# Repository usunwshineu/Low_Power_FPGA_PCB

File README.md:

# ICE40UP5K LOW POWER FPGA BOARD 

## PCB design

A custom low-power FPGA development board based on the Lattice iCE40UP5K FPGA. 
The board was designed to provide FPGA processing capabilities together with 
power monitoring and common communication interfaces.

The board contains:
* ICE40UP5K FPGA
* FTDI USB interface
* 12MHz clock (used for both the FPGA and FTDI)
* INA226 sensors for measuring power consumption
* I2C and SPI mode 0 PMODs
* SPI Flash memory
* I/O pins
* a reset button
* 3 buttons
* 4 LEDs and 1 RGB LED
  
For different SPI modes you can check <a href="https://0x04.net/~mwk/sbdocs/ice40/FPGA-TN-02010-1-8-iCE40-I2C-and-SPI-Hardened-IP-User-Guide.pdf">this document.

The final assembled board:

## PCB programming 

I checked the functionality of the board by running some simple verilog and I used icestorm for creating the bitstream. 
You can check more about Project IceStorm here <a href="https://0x04.net/~mwk/sbdocs/ice40/FPGA-TN-02010-1-8-iCE40-I2C-and-SPI-Hardened-IP-User-Guide.pdf](https://prjicestorm.readthedocs.io/en/latest/overview.html#what-is-project-icestorm">.

The commands I used were: 
* yosys -p "synth_ice40 -top top -json module.json" module.v -> for synthesizing the verilog design
* nextpnr-ice40 --up5k --package sg48 --json module.json --pcf pins.pcf --asc module.asc -> place-and-route
* icepack module.asc module.bin -> converting the result into binary bitstream
* iceprog module.bin -> programming the SPI Flash

Replace module.v, module.json, module.asc, module.bin, and pins.pcf with the corresponding filenames for your design.

## Adding a microprocessor

I used this particular RISC V system, which was built specifically for iCE40UP5k FPGAs: <a href="https://github.com/emeb/up5k_riscv/blame/master/README.md">up5k_riscv.

I modified the icestorm/up5k_riscv.pcf file with my own pins. Any other modified files were added to this repository.
In main.c file I wrote a code to read the power consumption (using I2C communication with the INA226 sensors) and display it on an OLED (SPI communication). 

This provides a complete demonstration of the board's:

* RISC V processing system
* I2C communication
* SPI communication
* Power monitoring
* OLED display interface

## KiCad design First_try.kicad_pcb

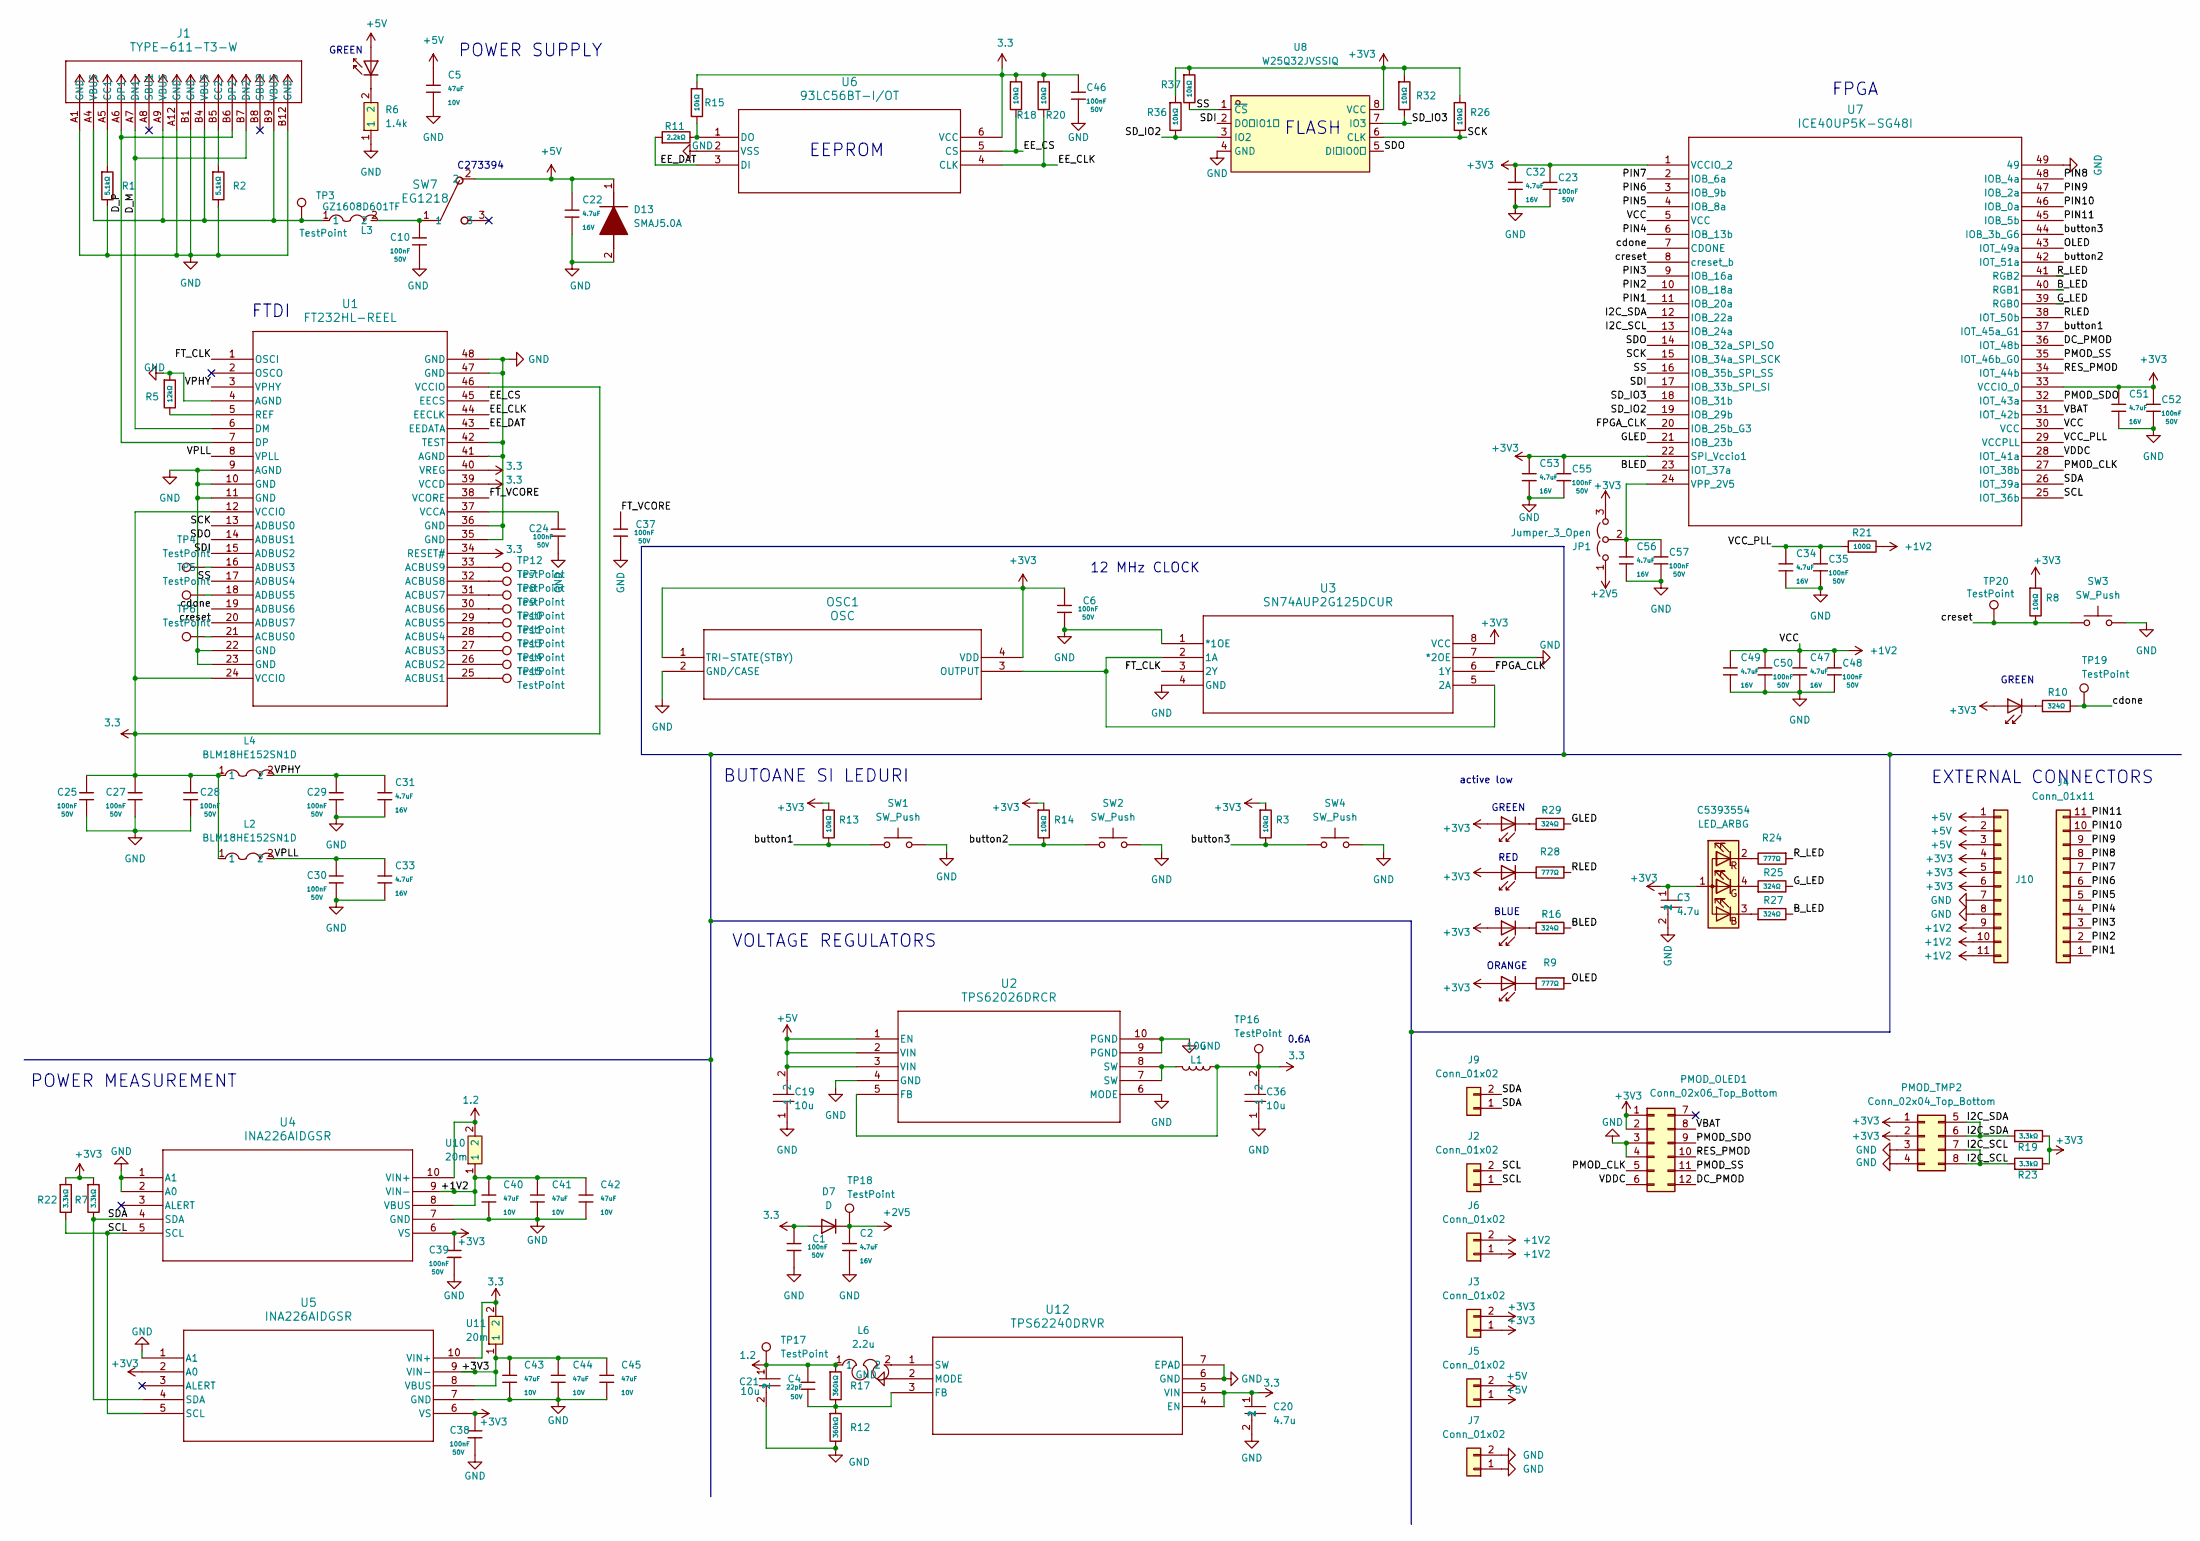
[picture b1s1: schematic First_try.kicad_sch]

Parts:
C1, C6, C10, C23, C24, C25, C27, C28, C29, C30, C35, C37, C38, C39, C46, C48, C50, C52, C55, C57: 100nF; C_0603; Voltage Rated 50V; Tolerance ±10%; Part CC0603KRX7R9BB104; LCSC C14663
C2, C22, C31, C32, C33, C34, C47, C49, C51, C53, C56: 4.7uF; C_0603; Voltage Rated 16V; Tolerance ±10%; Part CL10A475KO8NNNC; LCSC C19666
C3, C20: 4.7u; C_0603; LCSC Part C71631
C4: 22pF; C_0603; Voltage Rated 50V; Tolerance ±5%; Part CL10C220JB8NNNC; LCSC C1653
C5, C40, C41, C42, C43, C44, C45: 47uF; C_1206; Voltage Rated 10V; Tolerance ±20%; Part CL31A476MPHNNNE; LCSC C96123
C19, C36: 10u; C_1206; LCSC Part C92789
C21: 10u; C_0603; LCSC Part C77041
C5393554: LED_ARBG; RGB_LED; JLCPCB C5393554
D1, D2, D3: LD274; LED-SMD_L1.0-W0.5-RD; JLCPCB C5875752
D4: LD274; D_0805; JLCPCB C5366382
D5: LD274; LED-SMD_L1.0-W0.5-RD; JLCPCB C5354973
D6: LD274; LED-SMD_L2.1-W1.0-FD_UMD960; JLCPCB C5588281
D7: D; D2V5; JLCPCB C727112
D13: SMAJ5.0A; SMAJ; Manufacturer_Part_Number SMAJ5.0A; Mouser Part Number 652-SMAJ5.0A
J1: TYPE-611-T3-W; USB_C_Receptacle_HCTL_HC-TYPE-C-16P-01A; JLCPCB C2689844
J2, J3, J5, J6, J7, J9: Conn_01x02; PinHeader_1x02_P2.54mm_Vertical; JLCPB C32713268
J4, J10: Conn_01x11; PinHeader_1x11_P2.54mm_Vertical
JP1: Jumper_3_Open; PinHeader_1x03_P1.27mm_Vertical; JLCPCB C24980
L1: 10u; L_APV_ANR6045; JLCPCB C5259068
L2, L4: BLM18HE152SN1D; L_0603; LCSC Part C82155
L3: GZ1608D601TF; L_0603; LCSC Part C1002
L6: 2.2u; IND-SMD_L3.0-W3.0_LPS3015-222ML; LCSC Part C2844756
OSC1: OSC; ASE-3.2X2.5_ABR; JLCPCB C596950
PMOD_OLED1: Conn_02x06_Top_Bottom; PinSocket_2x06_P2.54mm_Horizontal_edit; JLCPCB C5333437
PMOD_TMP2: Conn_02x04_Top_Bottom; PinSocket_2x04_P2.54mm_Horizontal_edit; JLCPCB C7529541
R1, R2: 5.1kΩ; R_0603; Overload Voltage (Max) 75V; Tolerance ±1%; Part 0603WAF5101T5E; LCSC C23186
R3, R8, R13, R14, R15, R18, R20, R26, R32, R36, R37: 10kΩ; R_0603; Overload Voltage (Max) 75V; Tolerance ±1%; Part 0603WAF1002T5E; LCSC C25804
R5: 12kΩ; R_0603; Overload Voltage (Max) 75V; Tolerance ±1%; Part 0603WAF1202T5E; LCSC C22790
R6: 1.4k; R_0603; LCSC Part C25957
R7, R19, R22, R23: 3.3kΩ; R_0603; Overload Voltage (Max) 75V; Tolerance ±1%; Part 0603WAF3301T5E; LCSC C22978
R9, R24, R28: 777Ω; R_0402; Overload Voltage (Max) 75V; Tolerance ±1%; Part 0603WAF1001T5E; LCSC C852914
R10, R16, R25, R27, R29: 324Ω; R_0603; Overload Voltage (Max) 75V; Tolerance ±1%; Part 0603WAF5600T5E; LCSC C12963
R11: 2.2kΩ; R_0603; Overload Voltage (Max) 75V; Tolerance ±1%; Part 0603WAF2201T5E; LCSC C4190
R12, R17: 360kΩ; R_0603; Overload Voltage (Max) 75V; Tolerance ±1%; Part 0603WAF3603T5E; LCSC C23146
R21: 100Ω; R_0603; Overload Voltage (Max) 75V; Tolerance ±1%; Part 0603WAF1000T5E; LCSC C22775
SW1, SW2, SW3, SW4: SW_Push; SW_push; JLCPCB C455095
SW7: EG1218; SW_1218_EWI; JLCPCB C273394
TP3, TP4, TP5, TP6, TP7, TP8, TP9, TP10, TP11, TP12, TP13, TP14, TP15, TP16, TP17, TP18, TP19, TP20: TestPoint; TestPoint_Pad_1.0x1.0mm
U1: FT232HL-REEL; FTDI; JLCPCB C51997
U2: TPS62026DRCR; Vreg3_3; JLCPCB C2071183
U3: SN74AUP2G125DCUR; Buffer; JLCPCB C2862074
U4, U5: INA226AIDGSR; INA226; JLCPCB C49851
U6: 93LC56BT-I/OT; EEPROM; JLCPCB C190271
U7: ICE40UP5K-SG48I; QFN48_L-ASC10_ICE40ULTRAPLUS_MACHXO2_LAT
U8: W25Q32JVSSIQ; FLASH; LCSC Part C82344
U10, U11: 20m; R20m; LCSC Part C4944045
U12: TPS62240DRVR; Vreg1_2; JLCPCB C398345

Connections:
1.2: C4.1, C21.1, L6.1, R17.1, TP17.1, U4.10 (VIN+), U10.2
3.3: C1.1, C20.1, C25.1, C27.1, C28.1, C36.2, C46.1, D7.2 (A), L1.1, L2.1, L4.1, R15.1, R18.1, R20.1, TP16.1, U1.12 (VCCIO), U1.24 (VCCIO), U1.34 (RESET#), U1.39 (VCCD), U1.40 (VREG), U1.46 (VCCIO), U2.5 (FB), U5.10 (VIN+), U6.6 (VCC), U11.2, U12.4 (EN), U12.5 (VIN)
+1V2: C40.1, C41.1, C42.1, C47.1, C48.1, C49.1, C50.1, J6.1, J6.2, J10.9, J10.10, J10.11, R21.2, U4.8 (VBUS), U4.9 (VIN-), U7.5 (VCC), U7.30 (VCC), U10.1
+2V5: C2.1, D7.1 (K), JP1.1 (A), TP18.1
+3V3: C3.1, C6.1, C23.1, C32.1, C38.1, C39.1, C43.1, C44.1, C45.1, C51.1, C52.1, C53.1, C55.1, C5393554.1 (A), D1.2 (A), D3.2 (A), D4.2 (A), D5.2 (A), D6.2 (A), J3.1, J3.2, J10.4, J10.5, J10.6, JP1.3 (B), OSC1.1 (TRI-STATE(STBY)), OSC1.4 (VDD), PMOD_OLED1.1, PMOD_OLED1.2, PMOD_TMP2.1, PMOD_TMP2.2, R3.1, R7.1, R8.1, R13.1, R14.1, R19.2, R22.1, R23.2, R26.1, R32.1, R36.1, R37.1, U3.8 (VCC), U4.6 (VS), U5.2 (A0), U5.6 (VS), U5.8 (VBUS), U5.9 (VIN-), U7.1 (VCCIO_2), U7.22 (SPI_Vccio1), U7.33 (VCCIO_0), U8.8 (VCC), U11.1; also elsewhere on the board
+5V: C5.1, C19.2, C22.1, D2.2 (A), D13.1 (K), J5.1, J5.2, J10.1, J10.2, J10.3, SW7.2, U2.1 (EN), U2.2 (VIN), U2.3 (VIN)
/BLED: R16.2, U7.23 (IOT_37a)
/B_LED: R27.2, U7.40 (RGB1)
/DC_PMOD: PMOD_OLED1.12, U7.36 (IOT_48b)
/D_M: J1.A7 (DN1), J1.B7 (DN2), U1.6 (DM)
/D_P: J1.A6 (DP1), J1.B6 (DP2), U1.7 (DP)
/EE_CLK: R20.2, U1.44 (EECLK), U6.4 (CLK)
/EE_CS: R18.2, U1.45 (EECS), U6.5 (CS)
/EE_DAT: R11.1, U1.43 (EEDATA), U6.3 (DI)
/FPGA_CLK: U3.6 (1Y), U7.20 (IOB_25b_G3)
/FT_CLK: U1.1 (OSCI), U3.3 (2Y)
/FT_VCORE: C37.1, U1.38 (VCORE)
/GLED: R29.2, U7.21 (IOB_23b)
/G_LED: R25.2, U7.39 (RGB0)
/I2C_SCL: PMOD_TMP2.7, PMOD_TMP2.8, R23.1, U7.13 (IOB_24a)
/I2C_SDA: PMOD_TMP2.5, PMOD_TMP2.6, R19.1, U7.12 (IOB_22a)
/OLED: R9.1, U7.43 (IOT_49a)
/PIN1: J4.1, U7.11 (IOB_20a)
/PIN2: J4.2, U7.10 (IOB_18a)
/PIN3: J4.3, U7.9 (IOB_16a)
/PIN4: J4.4, U7.6 (IOB_13b)
/PIN5: J4.5, U7.4 (IOB_8a)
/PIN6: J4.6, U7.3 (IOB_9b)
/PIN7: J4.7, U7.2 (IOB_6a)
/PIN8: J4.8, U7.48 (IOB_4a)
/PIN9: J4.9, U7.47 (IOB_2a)
/PIN10: J4.10, U7.46 (IOB_0a)
/PIN11: J4.11, U7.45 (IOB_5b)
/PMOD_CLK: PMOD_OLED1.5, U7.27 (IOT_38b)
/PMOD_SDO: PMOD_OLED1.9, U7.32 (IOT_43a)
/PMOD_SS: PMOD_OLED1.11, U7.35 (IOT_46b_G0)
/RES_PMOD: PMOD_OLED1.10, U7.34 (IOT_44b)
/RLED: R28.1, U7.38 (IOT_50b)
/R_LED: R24.1, U7.41 (RGB2)
/SCK: R26.2, U1.13 (ADBUS0), U7.15 (IOB_34a_SPI_SCK), U8.6 (CLK)
/SCL: J2.1, J2.2, R22.2, U4.5 (SCL), U5.5 (SCL), U7.25 (IOT_36b)
/SDA: J9.1, J9.2, R7.2, U4.4 (SDA), U5.4 (SDA), U7.26 (IOT_39a)
/SDI: U1.15 (ADBUS2), U7.17 (IOB_33b_SPI_SI), U8.2 (DO（IO1）)
/SDO: U1.14 (ADBUS1), U7.14 (IOB_32a_SPI_SO), U8.5 (DI（IO0）)
/SD_IO2: R36.2, U7.19 (IOB_29b), U8.3 (IO2)
/SD_IO3: R32.2, U7.18 (IOB_31b), U8.7 (IO3)
/SS: R37.2, U1.17 (ADBUS4), U7.16 (IOB_35b_SPI_SS), U8.1 (~CS)
/VBAT: PMOD_OLED1.8, U7.31 (IOT_42b)
/VCC_PLL: C34.1, C35.1, R21.1, U7.29 (VCCPLL)
/VDDC: PMOD_OLED1.6, U7.28 (IOT_41a)
/VPHY: C29.1, C31.1, L4.2, U1.3 (VPHY)
/VPLL: C30.1, C33.1, L2.2, U1.8 (VPLL)
/cdone: R10.2, TP19.1, U1.19 (ADBUS6), U7.7 (CDONE)
unnamed: C10.1, L3.2, SW7.1
unnamed: C5393554.3 (BK), R27.1
unnamed: C5393554.4 (GK), R25.1
unnamed: C5393554.2 (RK), R24.2
unnamed: D1.1 (K), R29.1
unnamed: D2.1 (K), R6.2
unnamed: D3.1 (K), R10.1
unnamed: D4.1 (K), R28.2
unnamed: D5.1 (K), R16.1
unnamed: D6.1 (K), R9.2
unnamed: J1.A5 (CC1), R1.1
unnamed: J1.B5 (CC2), R2.1
unnamed: J1.A4 (VBUS), J1.A9 (VBUS), J1.B4 (VBUS), J1.B9 (VBUS), L3.1, TP3.1
unnamed: C56.1, C57.1, JP1.2 (C), U7.24 (VPP_2V5)
unnamed: L1.2, U2.7 (SW), U2.8 (SW)
unnamed 68: OSC1.3 (OUTPUT), U3.2 (1A), U3.5 (2A); also elsewhere on the board
unnamed: TP6.1, U1.21 (ACBUS0)
unnamed: TP15.1, U1.25 (ACBUS1)
unnamed: TP14.1, U1.26 (ACBUS2)
unnamed: TP13.1, U1.27 (ACBUS3)
unnamed: TP11.1, U1.28 (ACBUS4)
unnamed: TP10.1, U1.29 (ACBUS5)
unnamed: TP9.1, U1.30 (ACBUS6)
unnamed: TP8.1, U1.31 (ACBUS7)
unnamed: TP7.1, U1.32 (ACBUS8)
unnamed: TP12.1, U1.33 (ACBUS9)
unnamed: TP4.1, U1.16 (ADBUS3)
unnamed: TP5.1, U1.18 (ADBUS5)
unnamed: R5.2, U1.5 (REF)
unnamed: C24.1, U1.37 (VCCA)
unnamed: R11.2, R15.2, U6.1 (DO)
unnamed: C4.2, R12.1, R17.2, U12.3 (FB)
unnamed: L6.2, U12.1 (SW)

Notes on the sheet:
POWER SUPPLY
C273394
ORANGE
FPGA
BLUE
EXTERNAL CONNECTORS
RED
EEPROM
GREEN
FTDI
GREEN
BUTOANE SI LEDURI
POWER MEASUREMENT
12 MHz CLOCK
0.6A
VOLTAGE REGULATORS
active low
FLASH

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
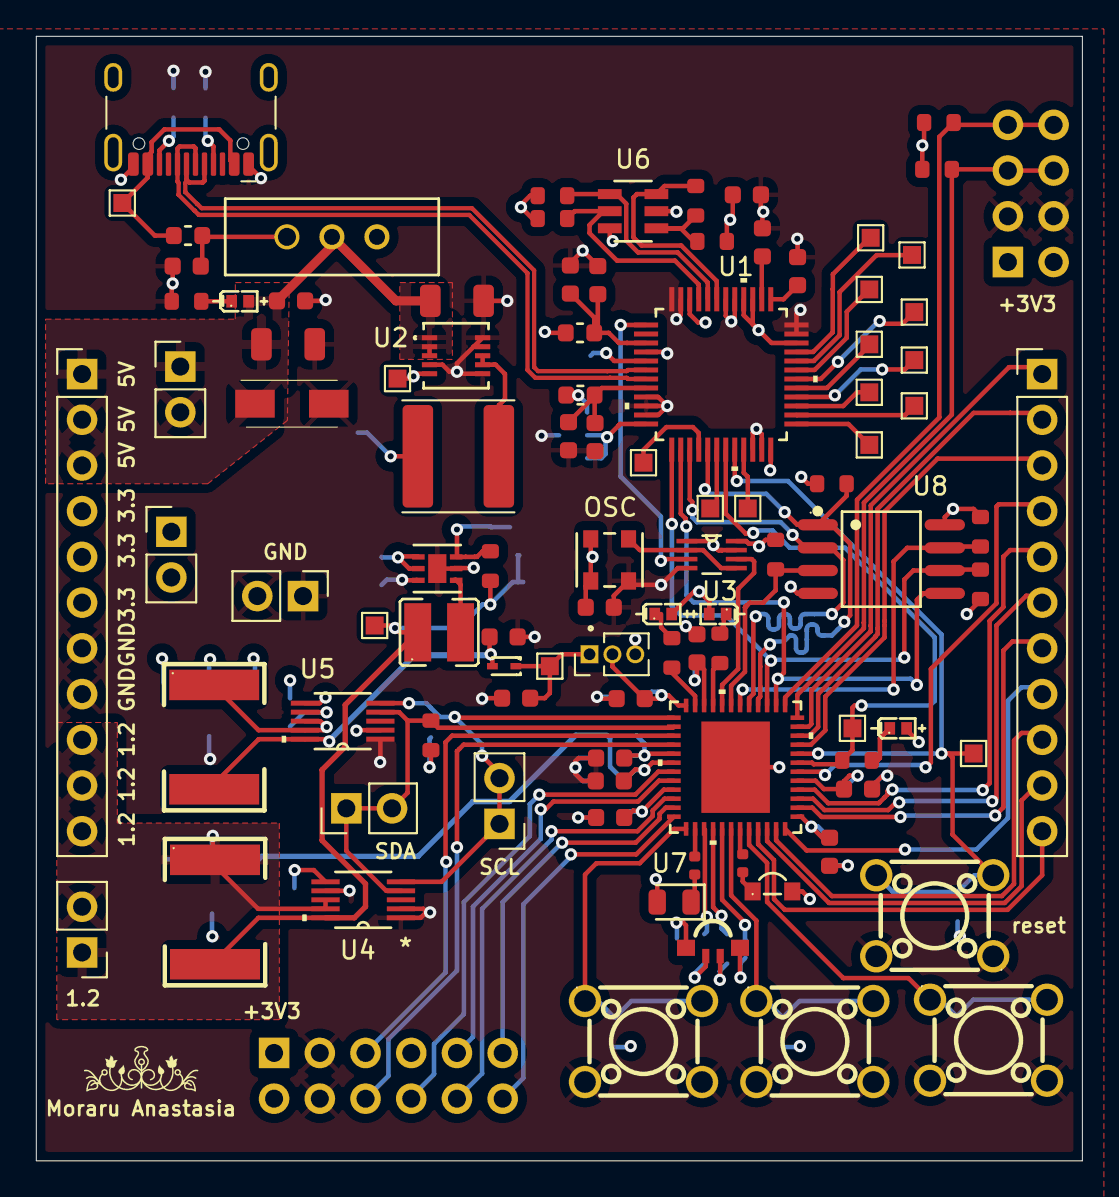
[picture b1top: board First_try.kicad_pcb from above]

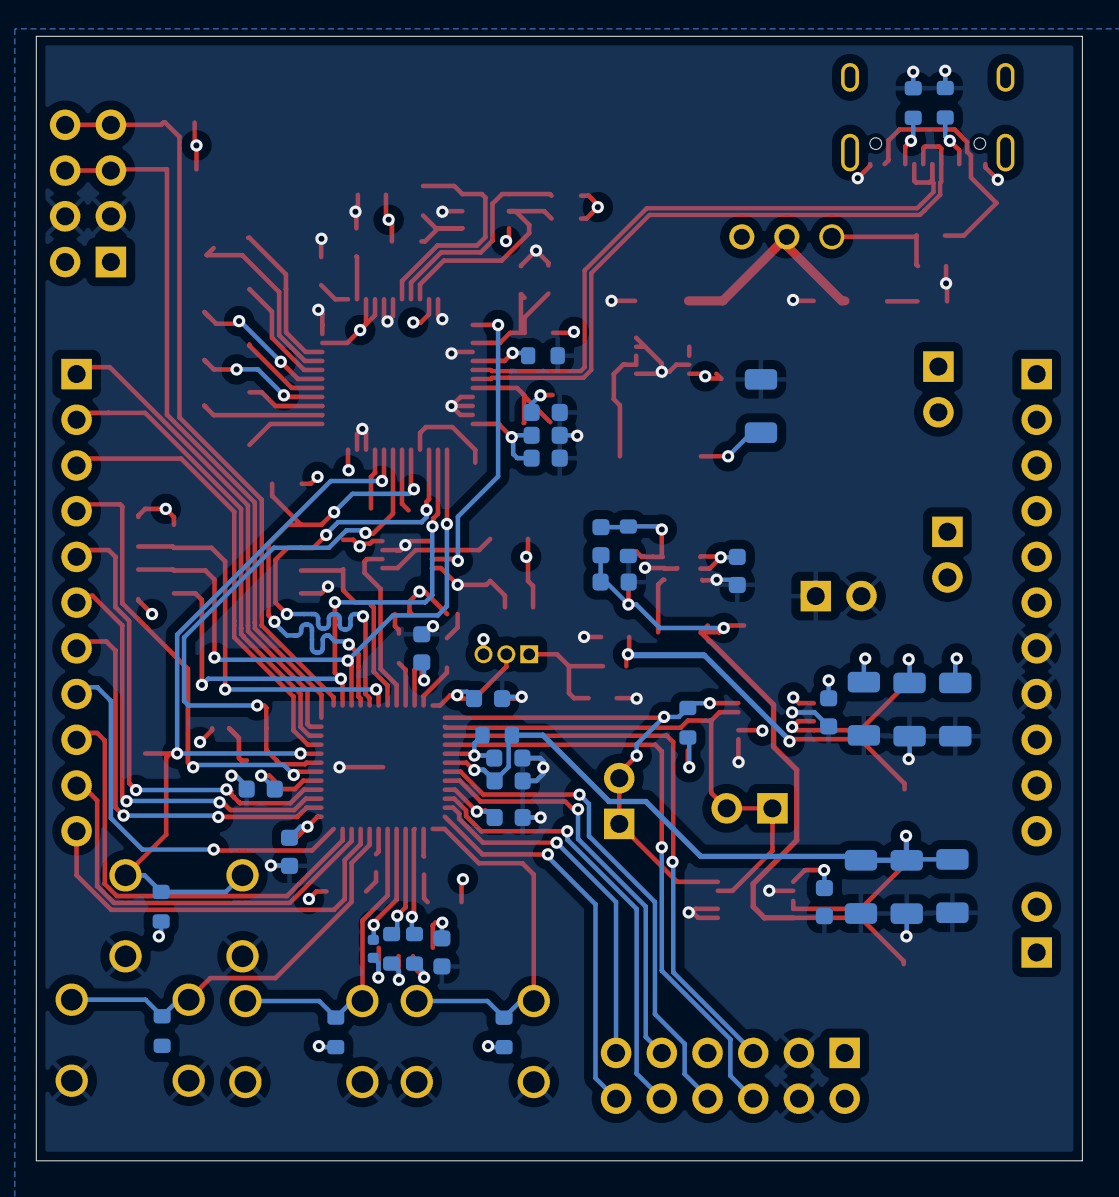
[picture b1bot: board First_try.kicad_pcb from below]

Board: 4 copper layers, 58.1 x 62.5 mm, 133 parts (36 on the bottom side), 83 nets.

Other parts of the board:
OSC: ASE-12.000MHZ-LC-T; ASE-3.2X2.5_ABR
R14#2: 10kΩ; R_0603
SW2#2: SW_Push; SW_push

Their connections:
+3V3: OSC.1 (TRI-STATE(STBY)), OSC.4 (VDD), R14#2.1; also elsewhere on the board
unnamed 68: OSC.3 (OUTPUT); also elsewhere on the board

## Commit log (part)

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2026-02-06 Initial project
2026-02-09 LEDs, Switches
2026-02-22 Reviewed USB-C plug
2026-03-01 Modificari dupa intalnirea de joi
2026-03-05 Replaced FPGA
2026-03-11 Modificari voltage regulator + LEDs
2026-03-11 Added external connectors
2026-03-13 Footprints added
2026-03-30 Started the layout
2026-03-30 Started Layout
2026-04-13 Layout modifications
2026-05-20 Last version
2026-06-10 RISC-V added
2026-06-18 i2c.c changes
2026-06-21 Create csmith
2026-06-21 Create folder
2026-06-21 Add main.c for picorv32 firmware initialization
2026-06-21 Add Makefile for icestorm project setup
